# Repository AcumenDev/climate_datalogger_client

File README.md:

# climate_datalogger_client
Клиент для системы мониторинга микроклимата в грибном производстве
Реализация клиента на esp

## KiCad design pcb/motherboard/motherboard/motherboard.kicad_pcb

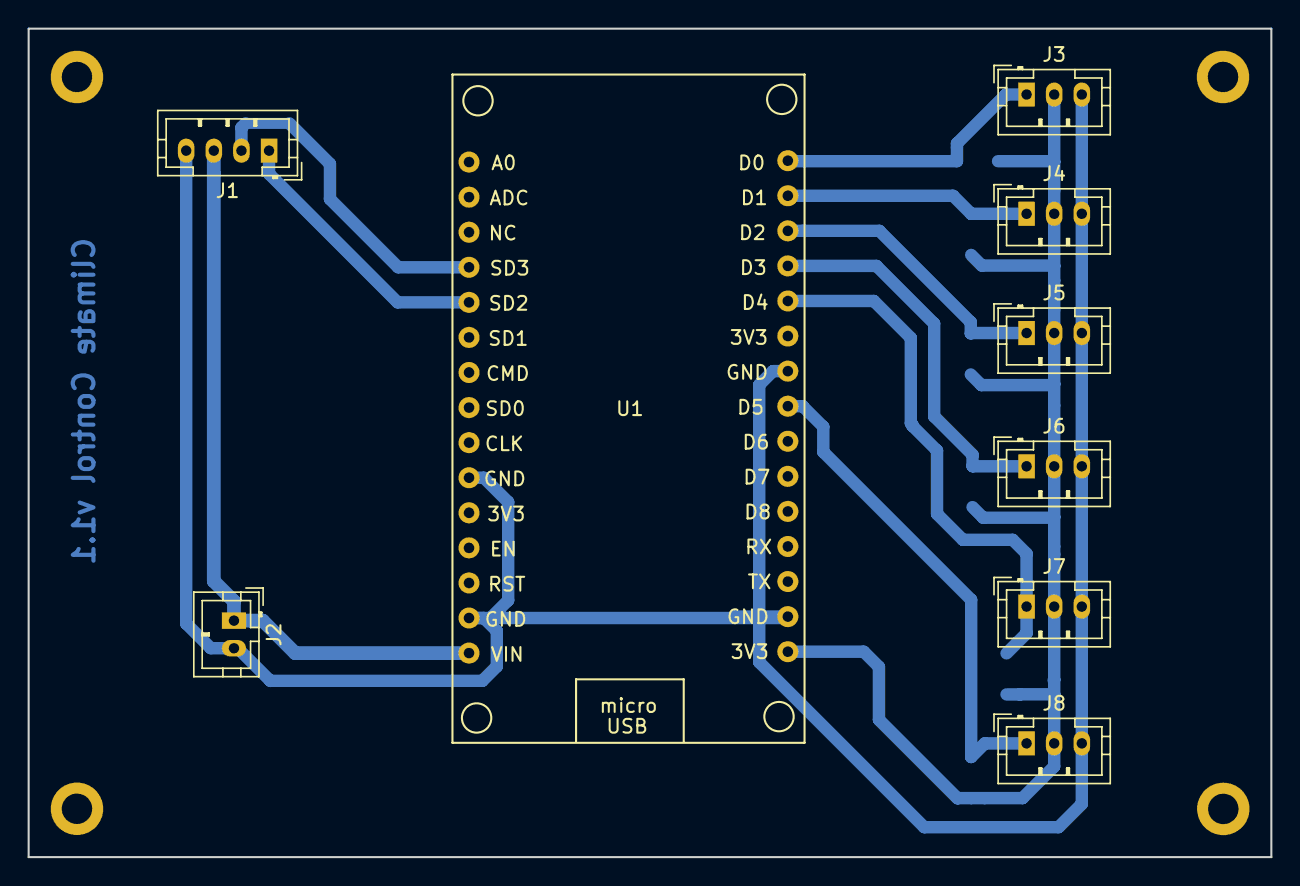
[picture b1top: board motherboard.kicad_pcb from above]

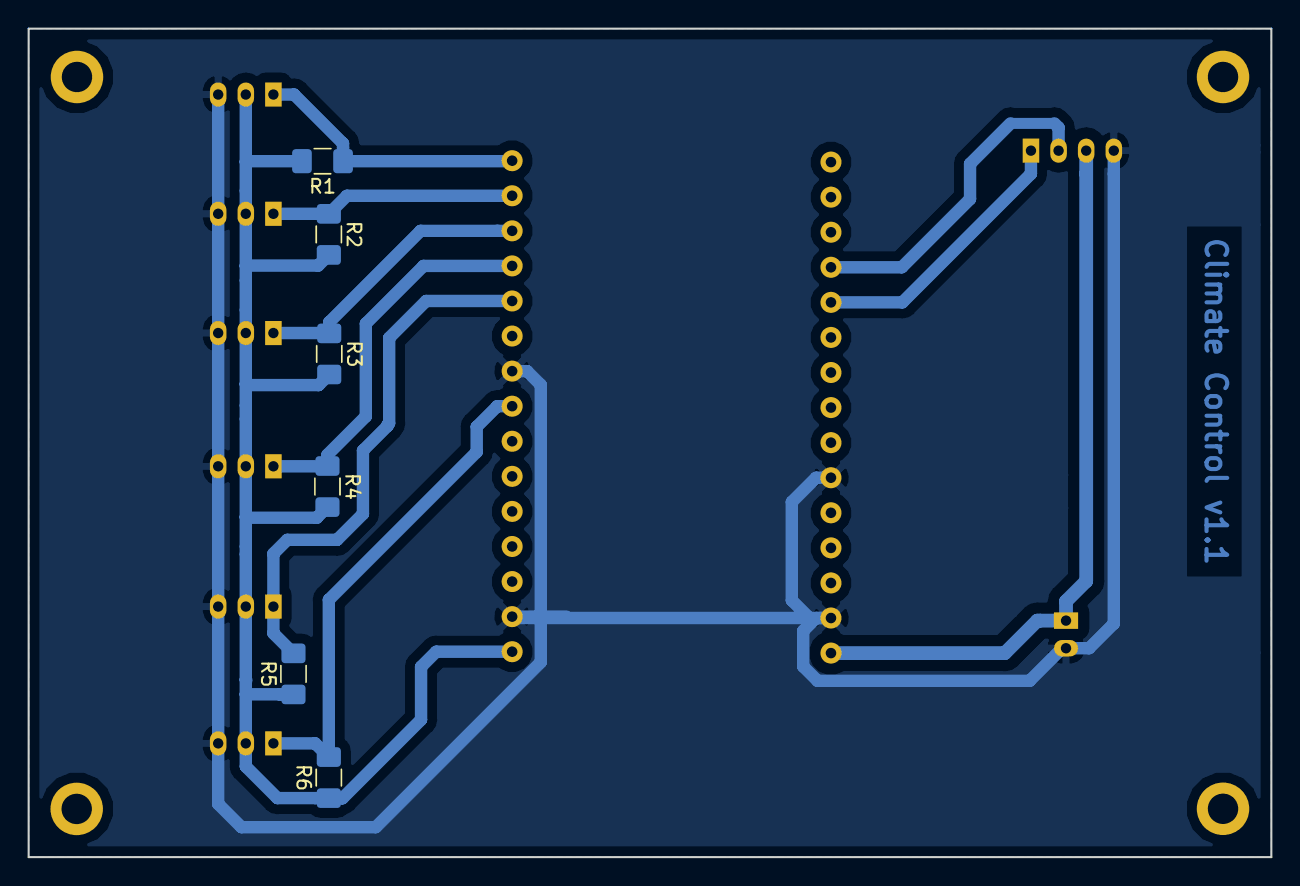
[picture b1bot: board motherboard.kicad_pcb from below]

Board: 2 copper layers, 90.0 x 60.0 mm, 15 parts (6 on the bottom side), 11 nets.

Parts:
J1: Display_01x04; JST_PH_B4B-PH-K_1x04_P2.00mm_Vertical
J2: Power_Conn_01x02; JST_PH_B2B-PH-K_1x02_P2.00mm_Vertical
J3, J4, J5, J6, J7, J8: Sensor_Conn_01x03; JST_PH_B3B-PH-K_1x03_P2.00mm_Vertical
R1, R2, R3, R4, R5, R6: 47k; R_1206_3216Metric_Pad1.42x1.75mm_HandSolder
U1: RobotDyn_NodeMCU

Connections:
3.3V: J3.2, J4.2, J5.2, J6.2, J7.2, J8.2, R1.2, R2.2, R3.2, R4.2, R5.1, R6.1, U1.16
GND: J1.4, J2.2, J3.3, J4.3, J5.3, J6.3, J7.3, J8.3, U1.10, U1.14, U1.17, U1.24
GPIO0: J6.1, R4.1, U1.27
GPIO2: J7.1, R5.2, U1.26
GPIO4: J5.1, R3.1, U1.28
GPIO5: J4.1, R2.1, U1.29
GPIO14: J8.1, R6.2, U1.23
GPIO16: J3.1, R1.1, U1.30
unnamed: J1.1, U1.5
unnamed: J1.2, U1.4
unnamed: J1.3, J2.1, U1.15

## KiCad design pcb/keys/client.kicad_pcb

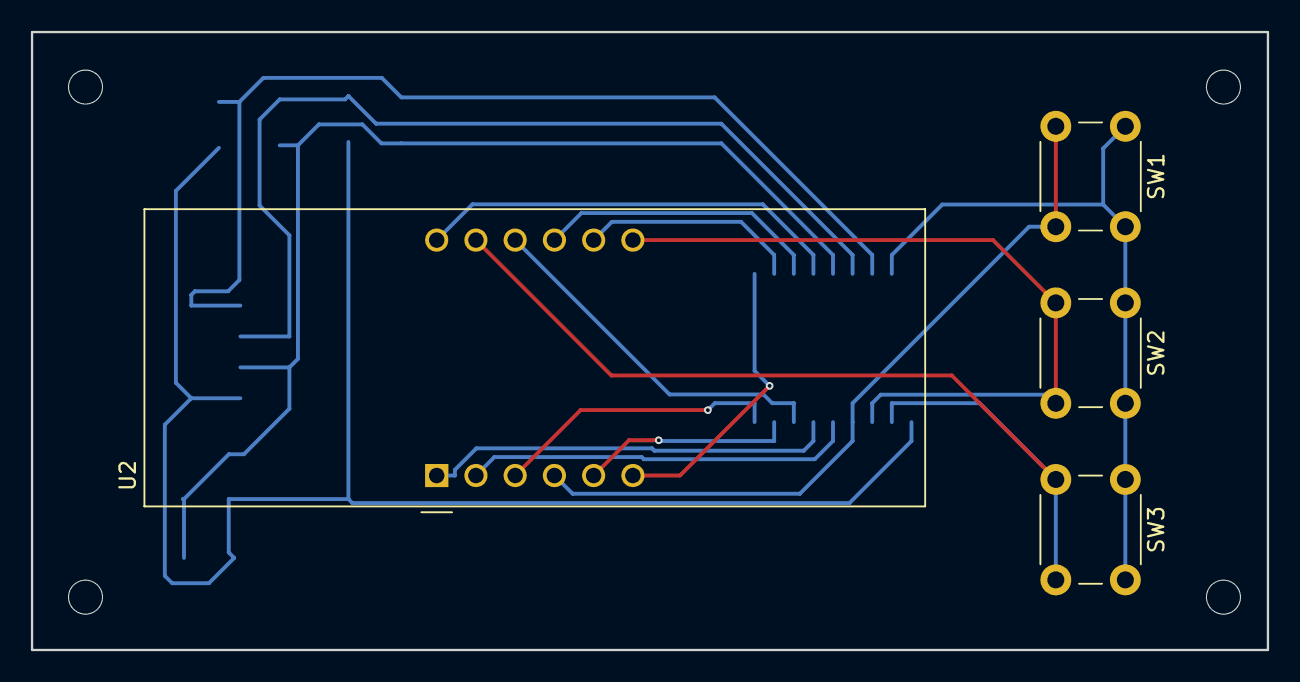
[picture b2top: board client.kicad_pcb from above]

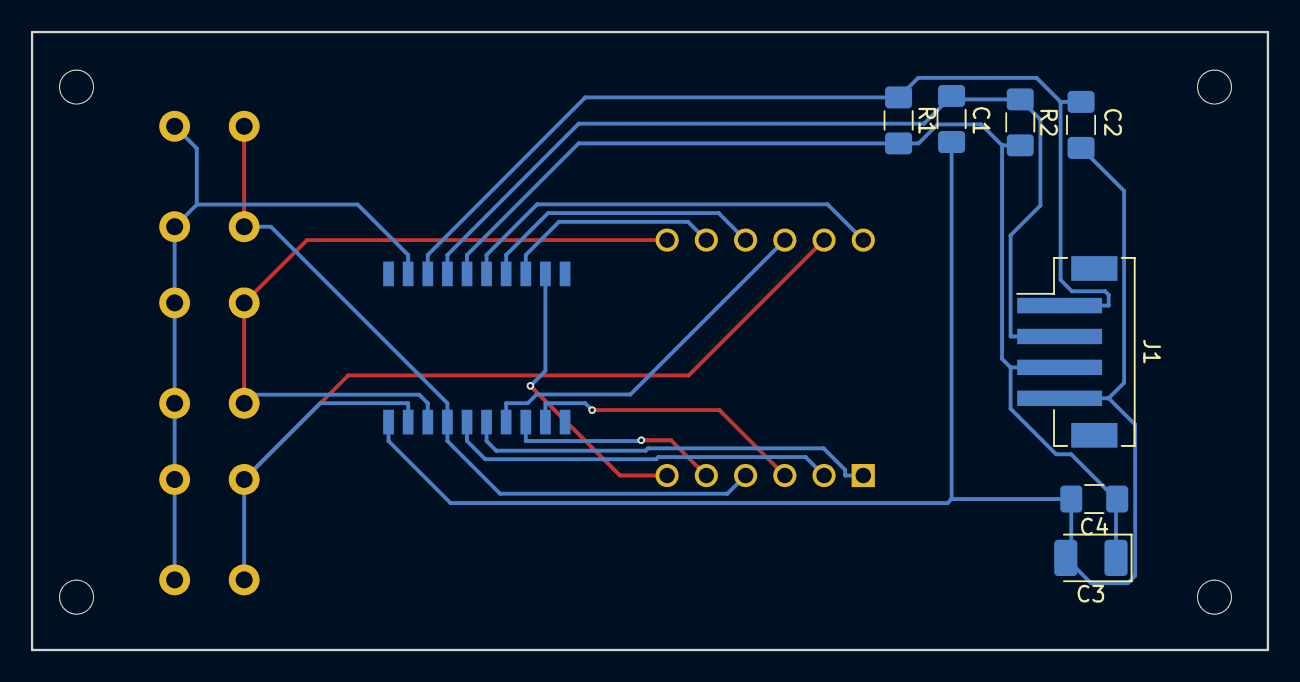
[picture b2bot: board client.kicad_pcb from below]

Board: 2 copper layers, 80.0 x 40.0 mm, 16 parts (8 on the bottom side), 17 nets.

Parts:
C1, C2: 100P; C_1206_3216Metric_Pad1.42x1.75mm_HandSolder
C3: 100uF; CP_EIA-3528-12_Kemet-T_Pad1.50x2.35mm_HandSolder
C4: 104; C_1206_3216Metric_Pad1.42x1.75mm_HandSolder
J1: Conn_01x04_Male; JST_PH_B4B-PH-SM4-TB_1x04-1MP_P2.00mm_Vertical
R1, R2: 10K; R_1206_3216Metric_Pad1.42x1.75mm_HandSolder
REF, REF1, REF2, REF3: MountingHole_2.2mm_M2
SW1: SW_Set; SW_PUSH_6mm_H9.5mm
SW2: SW_Plus; SW_PUSH_6mm_H9.5mm
SW3: SW_Minus; SW_PUSH_6mm_H9.5mm
U1: TM1637; SOP20
U2: CA56-12SEKWA; CA56-12SRWA

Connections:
GNDREF: C1.1, C2.1, C3.2, C4.2, J1.4, U1.1
unnamed: C1.2, J1.2, R2.1, U1.17
unnamed: C2.2, J1.1, R1.1, U1.18
unnamed: SW1.1, SW2.1, SW3.1, U1.19
unnamed: SW1.2, U1.4, U2.4
unnamed: SW2.2, U1.3, U2.7
unnamed: SW3.2, U1.2, U2.11
unnamed: U1.5, U2.2
unnamed: U1.6, U2.1
unnamed: U1.7, U2.10
unnamed: U1.8, U2.5
unnamed: U1.9, U2.3
unnamed: U1.12, U2.6
unnamed: U1.13, U2.8
unnamed: U1.14, U2.9
unnamed: U1.15, U2.12
VCC: C3.1, C4.1, J1.3, R1.2, R2.2, U1.16

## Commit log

2018-01-01 Реализация клиента на esp
2018-04-15 тест protobuf
2018-04-16 тесты с nanopb
2018-04-18 тесты с protobuf
2018-04-19 Запись пакета protobuf
2018-04-21 поддержание коннекта, пересылка показаний
2018-05-09 #2 страница настройки
2018-05-12 #2 close страница настройки
2018-05-22 #7 подключение датчика температуры ds18b20
2018-09-17 Тесты платы
2018-09-20 Новая разводка
2018-09-27 Отдал на производсво плату под дисплей
2018-10-28 Тесты дисплея
2018-11-03 #3 close, переехал на platformio, подключил дисплей
2018-11-11 Первая версия корпуса для печати
2018-11-11 #13 подготовил модели для печати
2018-12-09 #13 новый корпус
